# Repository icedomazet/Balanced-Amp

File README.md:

It should be 12V not 15V thats an error
R3 and R4 should be 270ohms

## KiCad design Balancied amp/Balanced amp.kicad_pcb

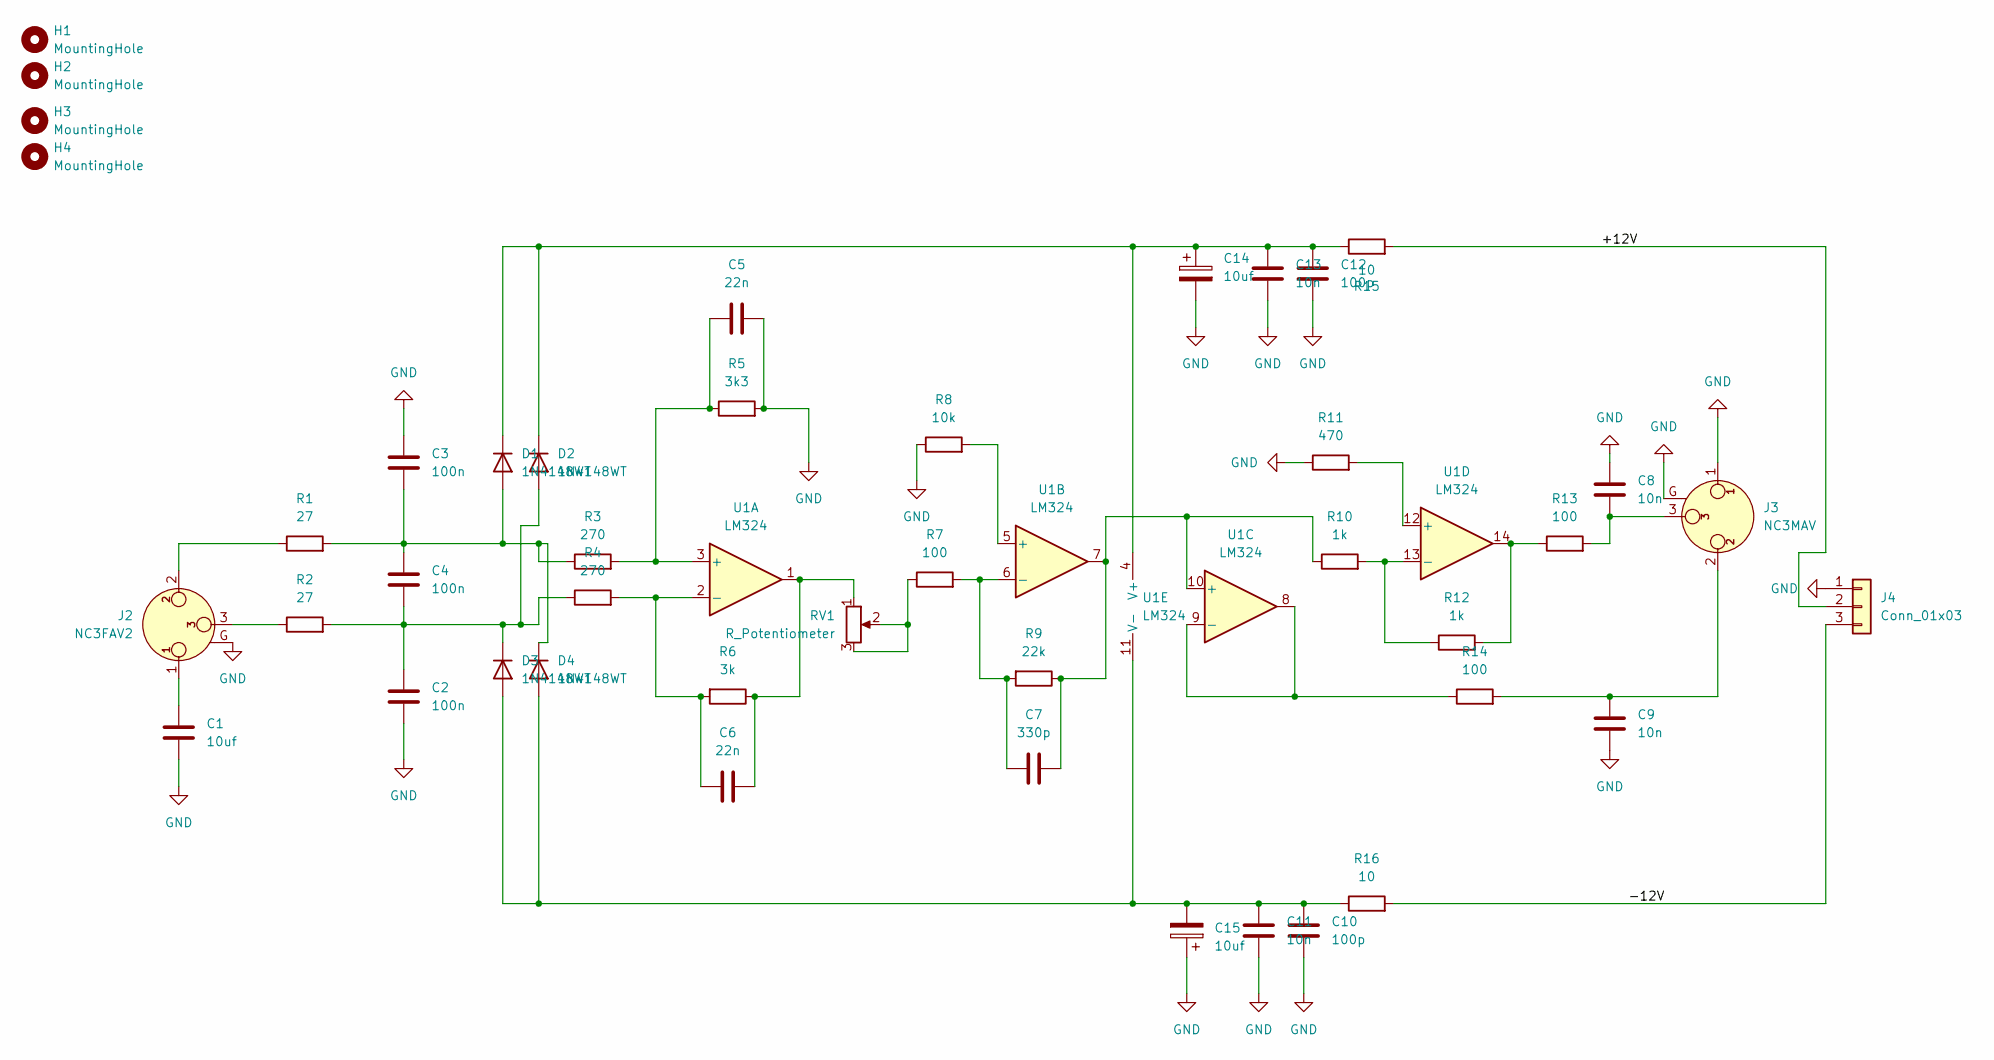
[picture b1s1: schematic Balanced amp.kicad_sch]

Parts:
C1: 10uf; C_Radial_D5.0mm_H5.0mm_P2.00mm
C2, C3, C4: 100n; C_Disc_D5.0mm_W2.5mm_P2.50mm
C5, C6: 22n; C_Disc_D5.0mm_W2.5mm_P2.50mm
C7: 330p; C_Disc_D5.0mm_W2.5mm_P2.50mm
C8, C9, C11, C13: 10n; C_Disc_D5.0mm_W2.5mm_P2.50mm
C10, C12: 100p; C_Disc_D5.0mm_W2.5mm_P2.50mm
C14, C15: 10uf; CP_Radial_D4.0mm_P2.00mm
D1, D2, D3, D4: 1N4148WT; D_5W_P12.70mm_Horizontal
H1, H2, H3, H4: MountingHole; MountingHole_2.7mm_M2.5_ISO14580
J2: NC3FAV2; Jack_XLR_Neutrik_NC3FAV2_Vertical
J3: NC3MAV; Jack_XLR_Neutrik_NC3MAV_Vertical
J4: Conn_01x03; TerminalBlock_MaiXu_MX126-5.0-03P_1x03_P5.00mm
R1, R2: 27; R_Axial_DIN0207_L6.3mm_D2.5mm_P10.16mm_Horizontal
R3, R4: 270; R_Axial_DIN0207_L6.3mm_D2.5mm_P10.16mm_Horizontal
R5: 3k3; R_Axial_DIN0207_L6.3mm_D2.5mm_P10.16mm_Horizontal
R6: 3k; R_Axial_DIN0207_L6.3mm_D2.5mm_P10.16mm_Horizontal
R7, R13, R14: 100; R_Axial_DIN0207_L6.3mm_D2.5mm_P10.16mm_Horizontal
R8: 10k; R_Axial_DIN0207_L6.3mm_D2.5mm_P10.16mm_Horizontal
R9: 22k; R_Axial_DIN0207_L6.3mm_D2.5mm_P10.16mm_Horizontal
R10, R12: 1k; R_Axial_DIN0207_L6.3mm_D2.5mm_P10.16mm_Horizontal
R11: 470; R_Axial_DIN0207_L6.3mm_D2.5mm_P10.16mm_Horizontal
R15, R16: 10; R_Axial_DIN0207_L6.3mm_D2.5mm_P10.16mm_Horizontal
RV1: R_Potentiometer; Potentiometer_Bourns_3296P_Horizontal
U1: LM324; DIP-14_W7.62mm_LongPads

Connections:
/+12V: J4.2, R15.2
/-12V: J4.3, R16.2
GND: C1.2, C2.2, C3.1, C5.2, C8.2, C9.1, C10.1, C11.1, C12.1, C13.1, C14.2, C15.1, J2.G, J3.1, J3.G, J4.1, R5.2, R8.1, R11.1
unnamed: C1.1, J2.1
unnamed: C6.1, R6.1, RV1.1, U1.1
unnamed: C8.1, J3.3, R13.2
unnamed: C9.2, J3.2, R14.2
unnamed: C3.2, C4.1, D1.2 (A), D4.1 (K), R1.2, R3.1
unnamed: C12.2, C13.2, C14.1, D1.1 (K), D2.1 (K), R15.1, U1.4 (V+)
unnamed: C2.1, C4.2, D2.2 (A), D3.1 (K), R2.2, R4.1
unnamed: C10.2, C11.2, C15.2, D3.2 (A), D4.2 (A), R16.1, U1.11 (V-)
unnamed: J2.2, R1.1
unnamed: J2.3, R2.1
unnamed: R7.1, RV1.2, RV1.3
unnamed: R12.2, R13.1, U1.14
unnamed: C5.1, R3.2, R5.1, U1.3 (+)
unnamed: C6.2, R4.2, R6.2, U1.2 (-)
unnamed: R8.2, U1.5 (+)
unnamed: C7.1, R7.2, R9.2, U1.6 (-)
unnamed: C7.2, R9.1, R10.1, U1.7, U1.10 (+)
unnamed: R14.1, U1.8, U1.9 (-)
unnamed: R11.2, U1.12 (+)
unnamed: R10.2, R12.1, U1.13 (-)

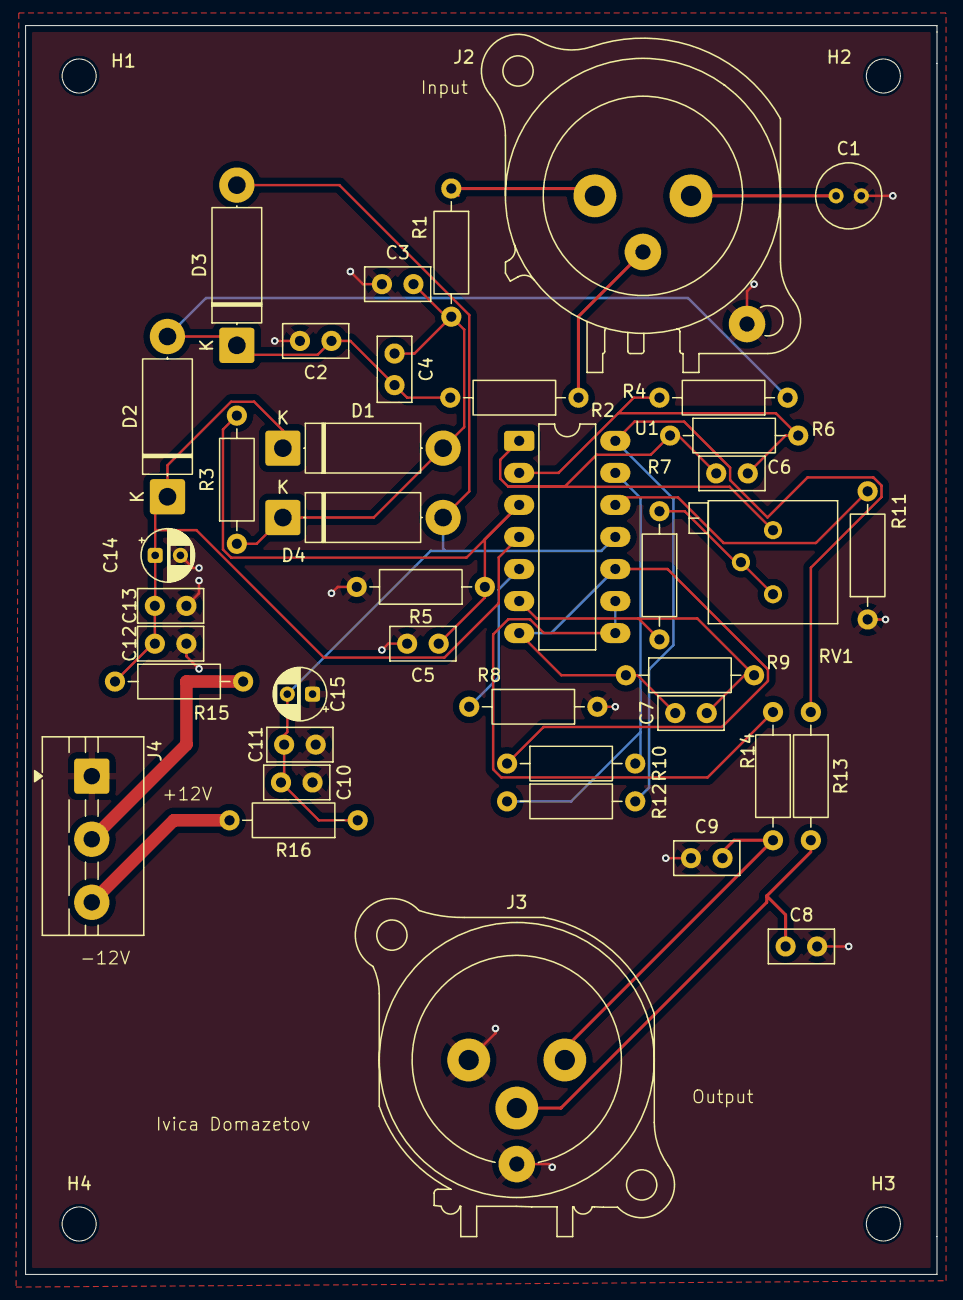
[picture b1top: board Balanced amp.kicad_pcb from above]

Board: 2 copper layers, 72.2 x 99.0 mm, 44 parts (0 on the bottom side), 23 nets.
